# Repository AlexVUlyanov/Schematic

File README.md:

# Schematic
Schematic module
- папка SMART LOCK UK - проект модуля доступа с базой данных по RFID - картам. Схемотехника выполнена в EAGLE CAD. В качестве микроконтроллера используется stm8L. Прогрманное обеспечение на МК выпонено в среде IAR язык С. Программно аппаратный комплекс делает учет времени входа и выхода сотрудника с занисением в баззу даных в виде файла. Программное обеспечения для ПК верхний уровень выполена в среде LABVIEW.
- Analog PID control - схемная реализация аналоговго ПИД регулятра на операционных усилителях EAGLE CAD.
- MIFA 868 MHz - антенна на чатоту 868 МГц модель в Ansys HFSS. 
- MIFA 2400 MHz - антенна на чатоту 2400 МГц модель в Ansys HFSS + согласование LC.
- AWR_Design_filter - пример заграждающего фильтра на 5 ГГц микрополосковый, среда разработки Cadence AWR Design Environment.
- GPS_patch_ceramic - пример модели GPS антенны и ее характеристики (Ansys) 
- Concentrator устройство обеспечивает чтение выходов типа сухой контакт сигнализаций и позволяет считывать их используя интерфейс Modbus RTU (RS-485). (Altium)
- Проект Horseradish PI - одноплатный компьбтер на базе SoC Allwinner H3, выполненный в OrCad Cadence.
- Altium_RK3588 - импортированный проект DEMO board RK3588 + топология печатного узла.

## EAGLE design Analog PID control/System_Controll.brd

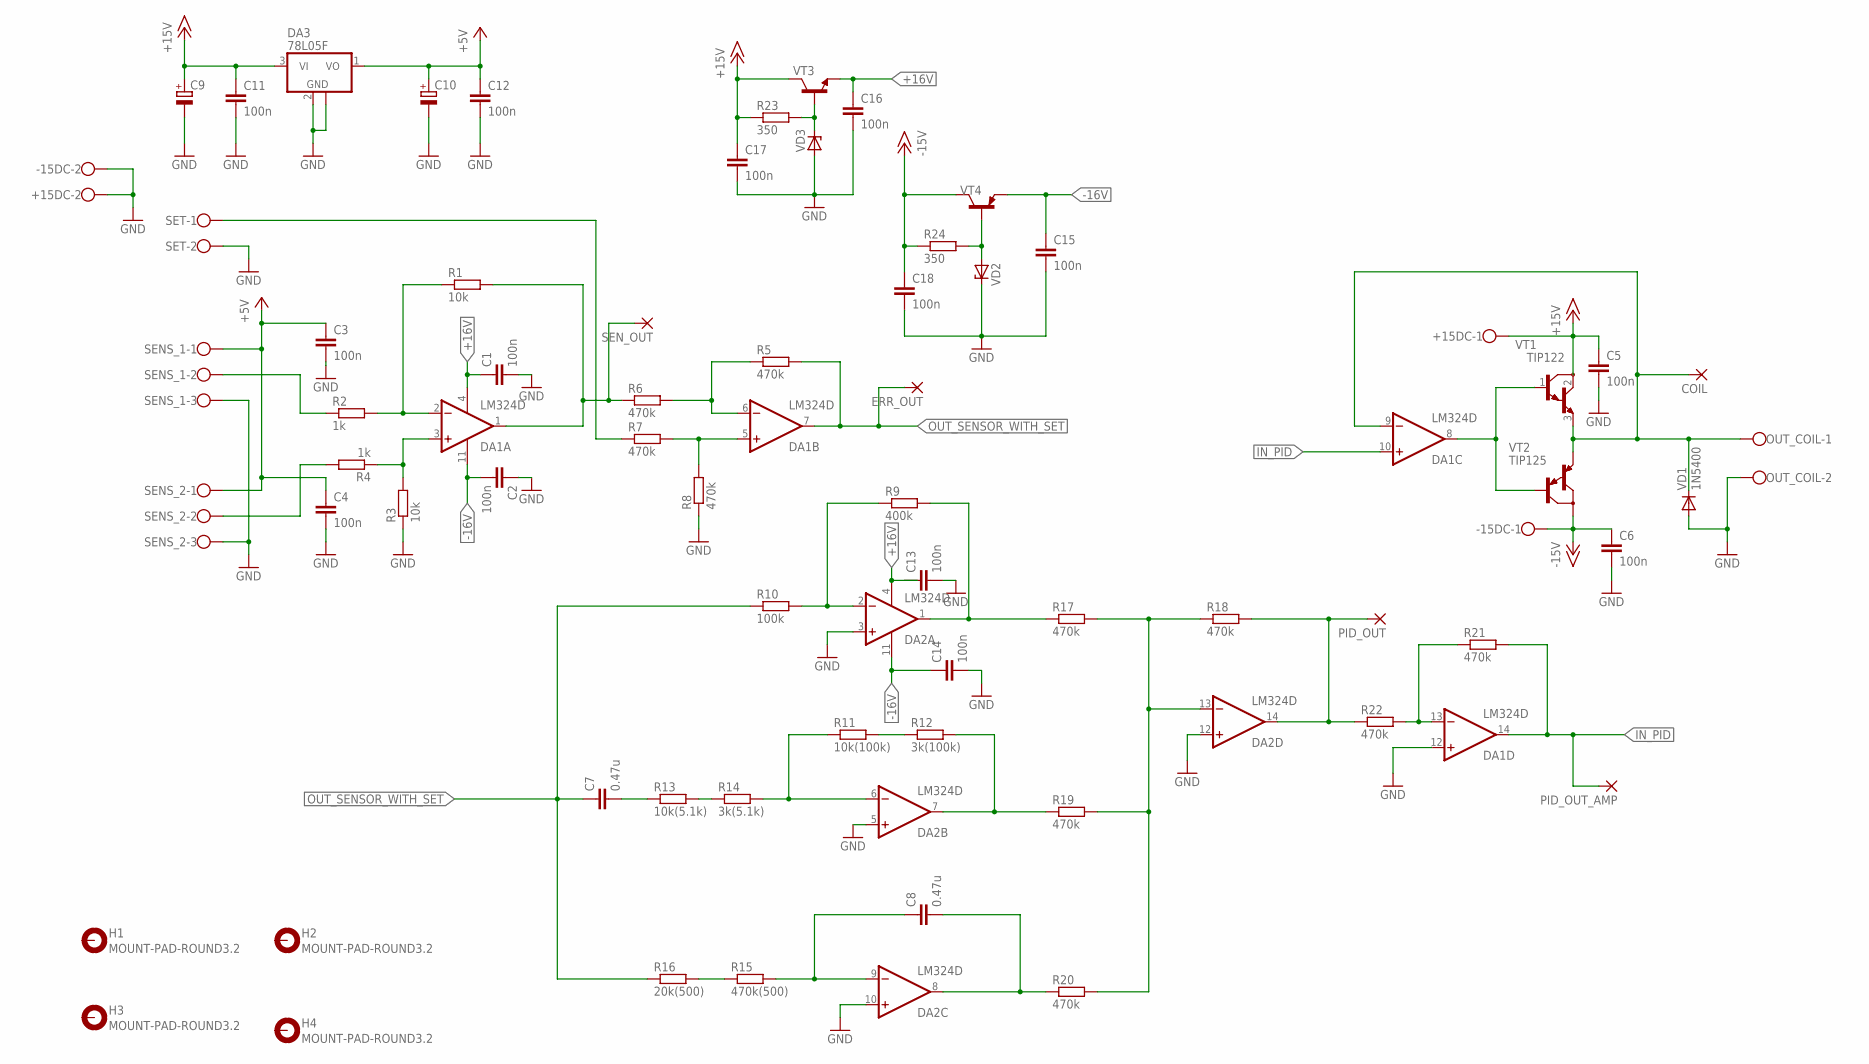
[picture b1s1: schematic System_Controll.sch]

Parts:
+15DC: W237-102
-15DC: W237-102
C1, C2, C3, C4, C5, C6, C11, C12, C13, C14, C15, C16, C17, C18: 100n; C1206
C7, C8: 0.47u; C1206
C9, C10: CPOL-EUE2,5-6; E2,5-6
COIL: PW_PAD
DA1, DA2: LM324D; SO14
DA3: 78L05F; SOT89
ERR_OUT: PW_PAD
H1, H2, H3, H4: MOUNT-PAD-ROUND3.2; 3,2-PAD
OUT_COIL: DG350-3.5-02P
PID_OUT: PW_PAD
PID_OUT_AMP: PW_PAD
R1, R3: 10k; M1206
R2, R4: 1k; M1206
R5, R6, R7, R8, R17, R18, R19, R20, R21, R22: 470k; M1206
R9: 400k; M1206
R10: 100k; M1206
R11: 10k(100k); M1206
R12: 3k(100k); M1206
R13: 10k(5.1k); M1206
R14: 3k(5.1k); M1206
R15: 470k(500); M1206
R16: 20k(500); M1206
R23, R24: 350; M1206
SENS_1, SENS_2: DG350-3.5-03P
SEN_OUT: PW_PAD
SET: DG350-3.5-02P
VD1: 1N5400; DO201-15
VD2, VD3: ZENER-DIODEDO41Z10; DO41Z10
VT1: TIP122; TO220
VT2: TIP125; TO220
VT3: BC847ALT1SMD; SOT23
VT4: BC807-16LT1SMD; SOT23-BEC

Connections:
+5V: C3.1, C4.1, C10.+, C12.1, DA3.1 (VO), SENS_1.1, SENS_2.1
+15V: +15DC.1, C5.1, C9.+, C11.1, C17.1, DA3.3 (VI), R23.1, VT1.2 (C), VT3.3 (C)
+16V: C1.1, C13.1, C16.1, DA1.4 (V+), DA2.4 (V+), VT3.2 (E)
-15V: -15DC.1, C6.1, C18.1, R24.1, VT2.2 (C), VT4.C
-16V: C2.2, C14.1, C15.1, DA1.11 (V-), DA2.11 (V-), VT4.E
COIL_OUT: COIL.P$1, DA1.9 (-IN), OUT_COIL.1, VD1.C, VT1.3 (E), VT2.3 (E)
GND: +15DC.2, -15DC.2, C1.2, C2.1, C3.2, C4.2, C5.2, C6.2, C9.-, C10.-, C11.2, C12.2, C13.2, C14.2, C15.2, C16.2, C17.2, C18.2, DA1.12 (+IN), DA2.3 (+IN), DA2.5 (+IN), DA2.10 (+IN), DA2.12 (+IN), DA3.2 (GND), DA3.2@1 (GND), OUT_COIL.2, R3.1, R8.1, SENS_1.3, SENS_2.3, SET.2, VD1.A, VD2.C, VD3.A
IN_PID: DA1.10 (+IN), DA1.14 (OUT), PID_OUT_AMP.P$1, R21.2
unnamed: DA1.1 (OUT), R1.2, R6.1, SEN_OUT.P$1
unnamed: DA1.2 (-IN), R1.1, R2.2
unnamed: DA1.3 (+IN), R3.2, R4.1
unnamed: R2.1, SENS_1.2
unnamed: R4.2, SENS_2.2
unnamed: DA2.2 (-IN), R9.1, R10.2
unnamed: R7.1, SET.1
unnamed: DA1.6 (-IN), R5.1, R6.2
unnamed: DA1.5 (+IN), R7.2, R8.2
unnamed: DA1.8 (OUT), VT1.1 (B), VT2.1 (B)
unnamed: DA2.1 (OUT), R9.2, R17.1
unnamed: R11.2, R12.1
unnamed: DA2.7 (OUT), R12.2, R19.1
unnamed: DA2.6 (-IN), R11.1, R14.2
unnamed: R13.2, R14.1
unnamed: C7.2, R13.1
unnamed: R24.2, VD2.A, VT4.B
unnamed: C8.2, DA2.8 (OUT), R20.1
unnamed: C8.1, DA2.9 (-IN), R15.2
unnamed: R15.1, R16.2
unnamed: DA2.13 (-IN), R17.2, R18.1, R19.2, R20.2
unnamed: DA2.14 (OUT), PID_OUT.P$1, R18.2, R22.1
unnamed: DA1.13 (-IN), R21.1, R22.2
unnamed: R23.2, VD3.C, VT3.1 (B)
OUT_SENSOR_WITH_SET: C7.1, DA1.7 (OUT), ERR_OUT.P$1, R5.2, R10.1, R16.1

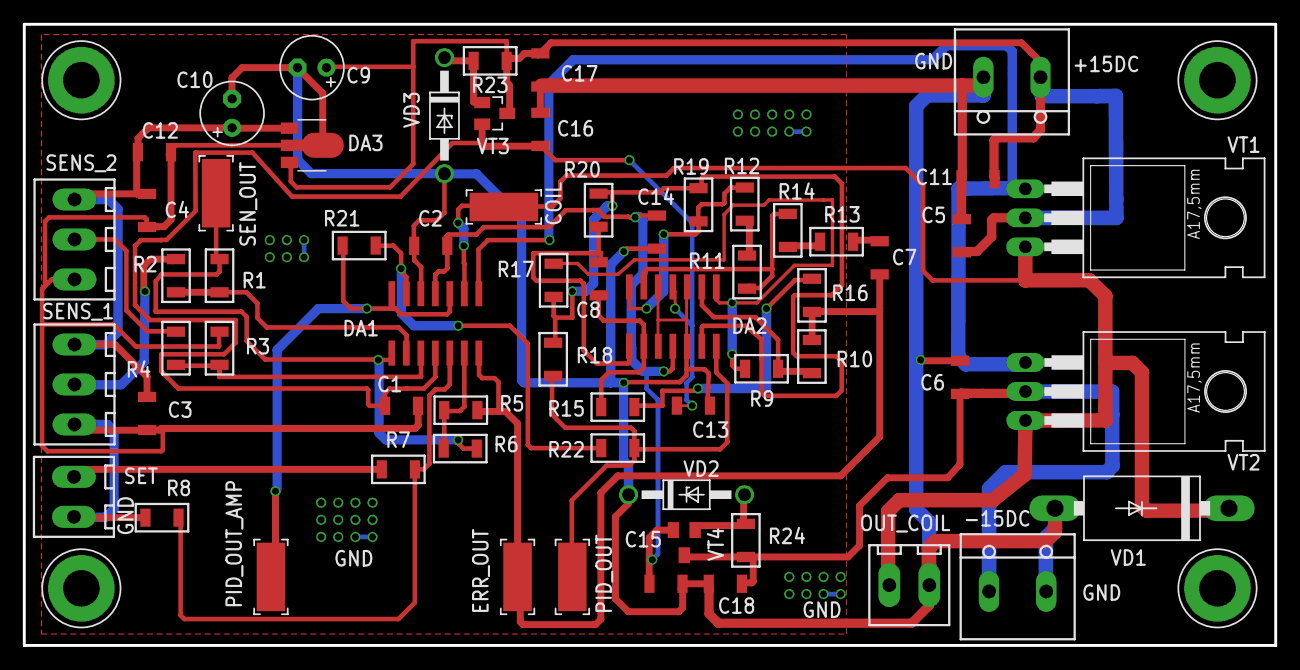
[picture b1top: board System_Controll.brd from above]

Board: 2 copper layers, 109.6 x 54.4 mm, 67 parts (0 on the bottom side), 33 nets.

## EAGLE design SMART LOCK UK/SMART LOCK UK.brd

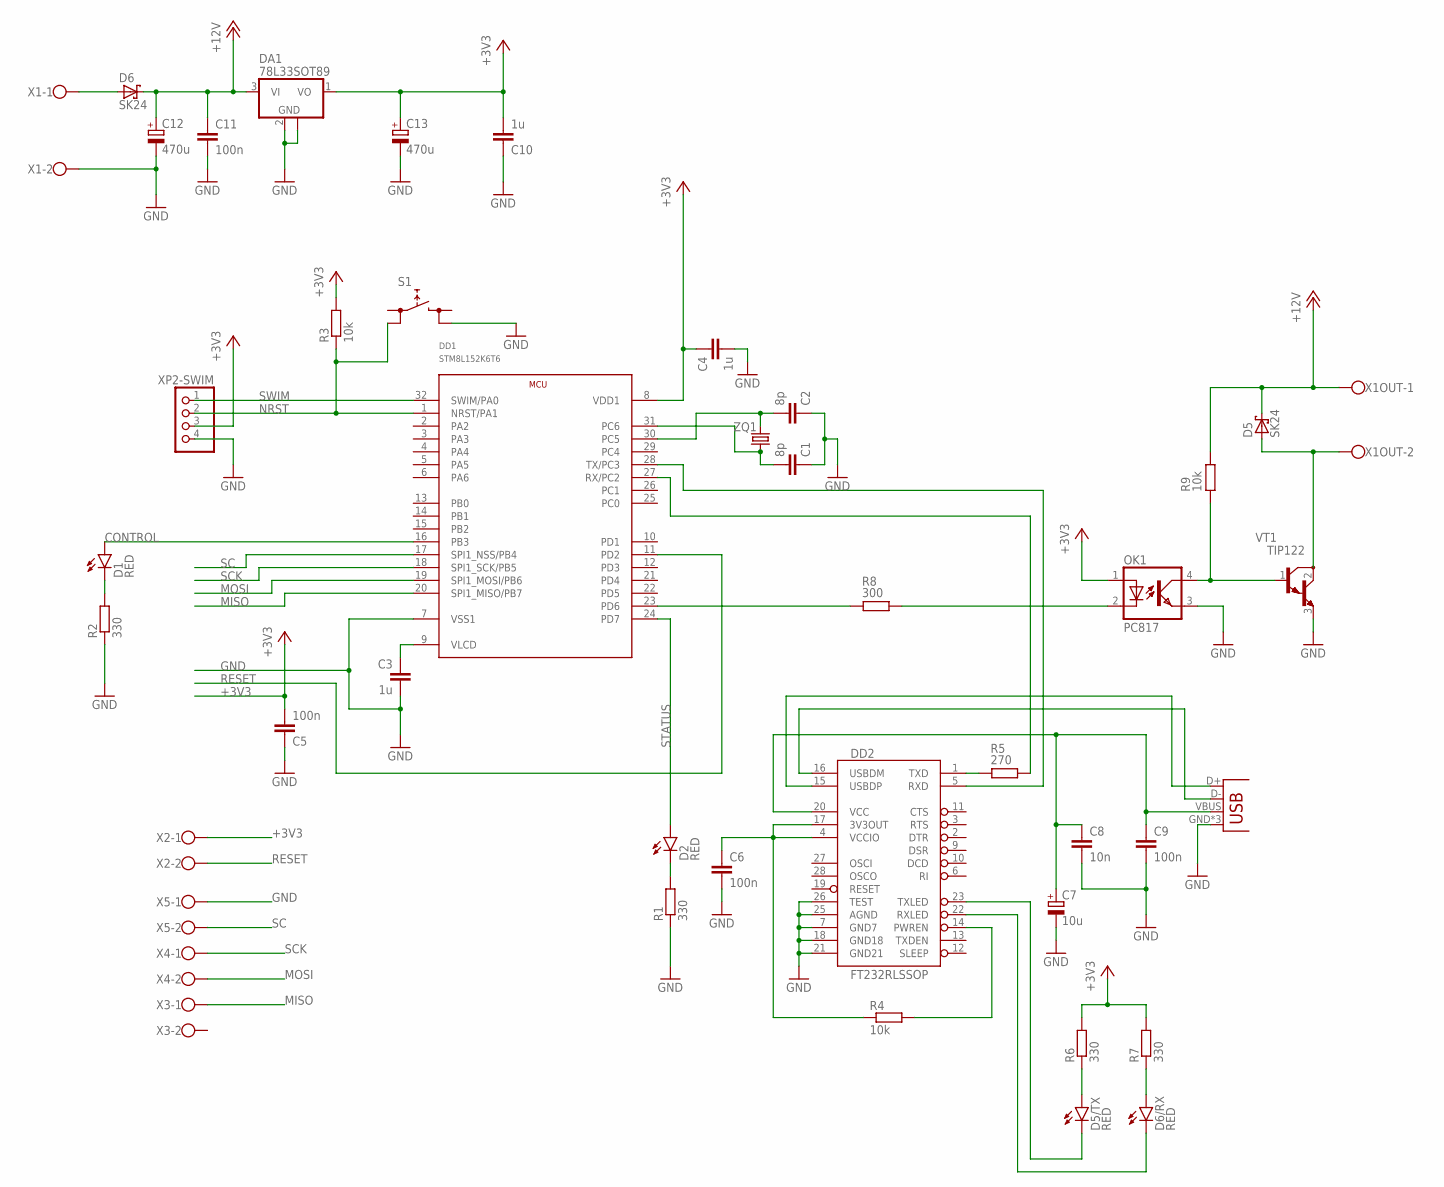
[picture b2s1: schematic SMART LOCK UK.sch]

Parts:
C1, C2: 8p; C1206
C3, C4, C10: 1u; C1206
C5, C6, C9, C11: 100n; C1206
C7: 10u; E2,5-5
C8: 10n; C1206
C12, C13: 470u; E3,5-8
D1, D2, D5/TX, D6/RX: RED; LED-1206
D5, D6: SK24; SMB
DA1: 78L33SOT89; SOT89
DD1: STM8L152K6T6; LQFP32-7X7
DD2: FT232RLSSOP; SSOP28DB
JP1: USB-B; USB-B-PTH
OK1: PC817; DIL04
R1, R2, R6, R7: 330; M1206
R3, R4, R9: 10k; M1206
R5: 270; M1206
R8: 300; M1206
S1: TACKT_SW_TH; TL1105
VT1: TIP122; TO220
X1, X1OUT: W237-102
X2, X3, X4, X5: DG350-3.5-02P
XP2-SWIM: PINHD-1X4; 1X04
ZQ1: CRYSTAL1MM20SS; MM20SS

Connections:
+3V3: C4.1, C5.2, C10.2, C13.+, DA1.1 (VO), DD1.8 (VDD1), OK1.1 (A), R3.2, R6.2, R7.2, X2.1, XP2-SWIM.3
+12V: C11.1, C12.+, D5.C, D6.C, DA1.3 (VI), R9.2, X1OUT.1
CONTROL: D1.A, DD1.16 (PB3)
GND: C1.1, C2.1, C3.2, C4.2, C5.1, C6.2, C7.-, C8.2, C9.2, C10.1, C11.2, C12.-, C13.-, DA1.2 (GND), DA1.2@1 (GND), DD1.7 (VSS1), DD2.7 (GND7), DD2.18 (GND18), DD2.21 (GND21), DD2.25 (AGND), DD2.26 (TEST), JP1.GND, JP1.S1 (GND), JP1.S2 (GND), OK1.3 (EMIT), R1.1, R2.1, S1.4 (1), VT1.3 (E), X1.2, X5.1, XP2-SWIM.4
MISO: DD1.20 (SPI1_MISO/PB7), X3.1
MOSI: DD1.19 (SPI1_MOSI/PB6), X4.2
unnamed: DD1.28 (TX/PC3), DD2.5 (RXD)
unnamed: C1.2, DD1.31 (PC6), ZQ1.1
unnamed: C3.1, DD1.9 (VLCD)
unnamed: D5/TX.A, R6.1
unnamed: D6/RX.A, R7.1
unnamed: D5/TX.C, DD2.23 (TXLED)
unnamed: D6/RX.C, DD2.22 (RXLED)
unnamed: D5.A, VT1.2 (C), X1OUT.2
unnamed: D2.C, R1.2
unnamed: D1.C, R2.2
unnamed: OK1.4 (COL), R9.1, VT1.1 (B)
unnamed: OK1.2 (C), R8.2
unnamed: DD1.23 (PD6), R8.1
unnamed: D6.A, X1.1
unnamed: C7.+, C8.1, C9.1, DD2.20 (VCC), JP1.VBUS
unnamed: DD1.27 (RX/PC2), R5.2
unnamed: C2.2, DD1.30 (PC5), ZQ1.4 (2)
unnamed: DD2.16 (USBDM), JP1.D-
unnamed: DD2.15 (USBDP), JP1.D+
unnamed: C6.1, DD2.4 (VCCIO), DD2.17 (3V3OUT), R4.1
unnamed: DD2.14 (PWREN), R4.2
unnamed: DD2.1 (TXD), R5.1
NRST: DD1.1 (NRST/PA1), R3.1, S1.3 (0), XP2-SWIM.2
RESET: DD1.11 (PD2), X2.2
SC: DD1.17 (SPI1_NSS/PB4), X5.2
SCK: DD1.18 (SPI1_SCK/PB5), X4.1
STATUS: D2.A, DD1.24 (PD7)
SWIM: DD1.32 (SWIM/PA0), XP2-SWIM.1

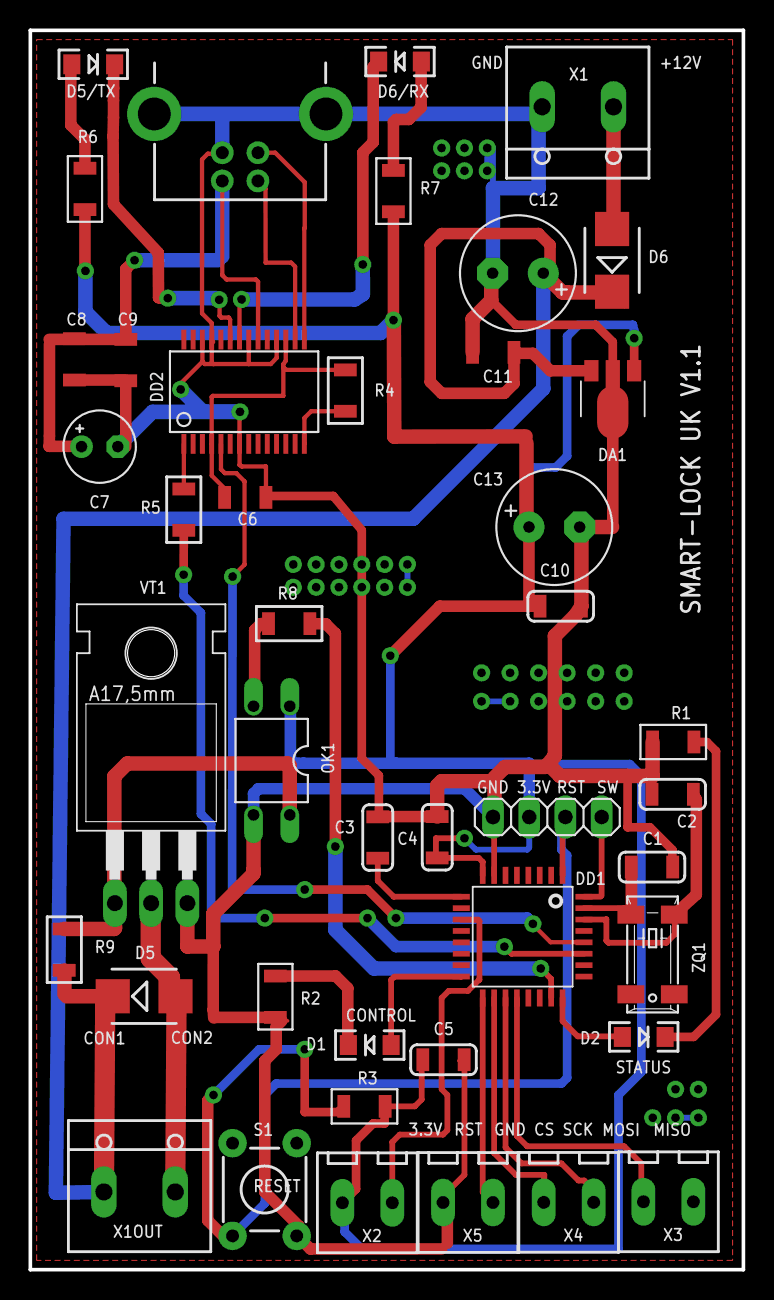
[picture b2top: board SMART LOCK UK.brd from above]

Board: 2 copper layers, 50.0 x 86.9 mm, 43 parts (0 on the bottom side), 34 nets.

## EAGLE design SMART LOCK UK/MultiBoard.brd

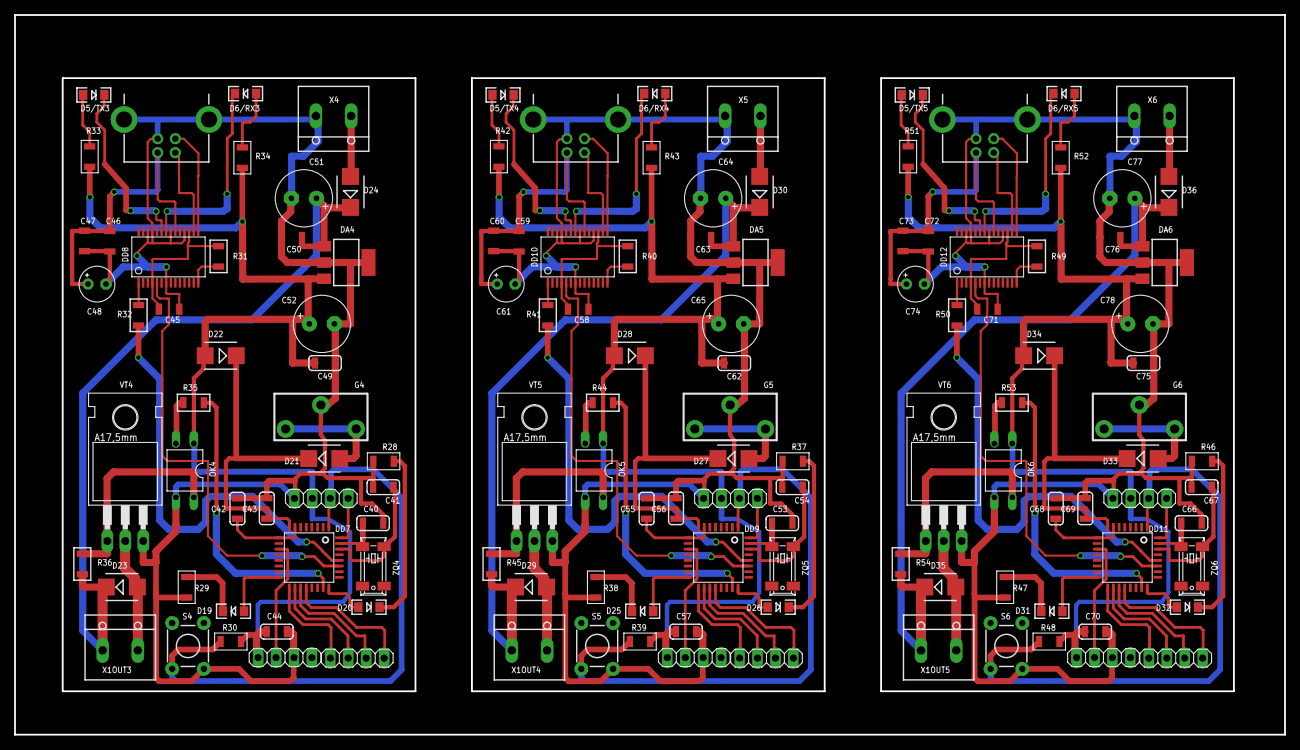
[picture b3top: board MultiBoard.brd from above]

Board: 2 copper layers, 180.0 x 102.0 mm, 132 parts (0 on the bottom side), 108 nets.

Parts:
C40, C41, C53, C54, C66, C67: 8p; C1206
C42, C43, C49, C55, C56, C62, C68, C69, C75: 1u; C1206
C44, C45, C46, C50, C57, C58, C59, C63, C70, C71, C72, C76: 100n; C1206
C47, C60, C73: 10n; C1206
C48, C61, C74: 10u; E2,5-5
C51, C52, C64, C65, C77, C78: 470u; E3,5-8
D5/TX3, D5/TX4, D5/TX5, D6/RX3, D6/RX4, D6/RX5, D19, D20, D25, D26, D31, D32: RED; LED-1206
D21, D22, D23, D24, D27, D28, D29, D30, D33, D34, D35, D36: SK24; SMB
DA4, DA5, DA6: APU1206H-33; SOT223
DD7, DD9, DD11: STM8L152K6T6; LQFP32-7X7
DD8, DD10, DD12: FT232RLSSOP; SSOP28DB
G4, G5, G6: BAT_3VCH-74; CH74
JP4, JP5, JP6: USB-B; USB-B-PTH
OK4, OK5, OK6: PC817; DIL04
R28, R29, R33, R34, R37, R38, R42, R43, R46, R47, R51, R52: 330; M1206
R30, R31, R39, R40, R48, R49: 10k; M1206
R32, R41, R50: 270; M1206
R35, R36, R44, R45, R53, R54: 1k; M1206
S4, S5, S6: TL1105
VT4, VT5, VT6: TIP122; TO220
X1OUT3, X1OUT4, X1OUT5, X4, X5, X6: W237-102
XP1.1-SPI3, XP1.1-SPI4, XP1.1-SPI5, XP1.2-SPI3, XP1.2-SPI4, XP1.2-SPI5, XP2-SWIM3, XP2-SWIM4, XP2-SWIM5: 1X04
ZQ4, ZQ5, ZQ6: MM20SS

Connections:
+3V4: C44.2, C49.2, C52.+, D22.A, DA4.3, OK4.1, R30.2, R33.2, R34.2, XP1.2-SPI3.4, XP2-SWIM3.3
+3V5: C57.2, C62.2, C65.+, D28.A, DA5.3, OK5.1, R39.2, R42.2, R43.2, XP1.2-SPI4.4, XP2-SWIM4.3
+3V6: C70.2, C75.2, C78.+, D34.A, DA6.3, OK6.1, R48.2, R51.2, R52.2, XP1.2-SPI5.4, XP2-SWIM5.3
+12V3: C50.1, C51.+, D23.C, D24.C, DA4.1, R36.2, X1OUT3.1
+12V4: C63.1, C64.+, D29.C, D30.C, DA5.1, R45.2, X1OUT4.1
+12V5: C76.1, C77.+, D35.C, D36.C, DA6.1, R54.2, X1OUT5.1
CONTROL3: D19.A, DD7.16
CONTROL4: D25.A, DD9.16
CONTROL5: D31.A, DD11.16
FT_RXD3: DD7.28, R32.2
FT_RXD4: DD9.28, R41.2
FT_RXD5: DD11.28, R50.2
FT_TXD3: DD7.27, DD8.5
FT_TXD4: DD9.27, DD10.5
FT_TXD5: DD11.27, DD12.5
GND3: C40.1, C41.1, C42.2, C43.2, C44.1, C45.2, C46.2, C47.2, C48.-, C49.1, C50.2, C51.-, C52.-, DA4.2, DA4.4, DD8.7, DD8.18, DD8.21, DD8.25, DD8.26, G4.P$3-, JP4.GND, JP4.S1, JP4.S2, OK4.3, R28.1, R29.1, S4.4, VT4.3, X4.2, XP1.2-SPI3.2, XP2-SWIM3.4
GND4: C53.1, C54.1, C55.2, C56.2, C57.1, C58.2, C59.2, C60.2, C61.-, C62.1, C63.2, C64.-, C65.-, DA5.2, DA5.4, DD10.7, DD10.18, DD10.21, DD10.25, DD10.26, G5.P$3-, JP5.GND, JP5.S1, JP5.S2, OK5.3, R37.1, R38.1, S5.4, VT5.3, X5.2, XP1.2-SPI4.2, XP2-SWIM4.4
GND5: C66.1, C67.1, C68.2, C69.2, C70.1, C71.2, C72.2, C73.2, C74.-, C75.1, C76.2, C77.-, C78.-, DA6.2, DA6.4, DD12.7, DD12.18, DD12.21, DD12.25, DD12.26, G6.P$3-, JP6.GND, JP6.S1, JP6.S2, OK6.3, R46.1, R47.1, S6.4, VT6.3, X6.2, XP1.2-SPI5.2, XP2-SWIM5.4
MISO3: DD7.20, XP1.1-SPI3.4
MISO4: DD9.20, XP1.1-SPI4.4
MISO5: DD11.20, XP1.1-SPI5.4
MOSI3: DD7.19, XP1.1-SPI3.3
MOSI4: DD9.19, XP1.1-SPI4.3
MOSI5: DD11.19, XP1.1-SPI5.3
unnamed: C40.2, DD7.31, ZQ4.1
unnamed: C42.1, DD7.7, DD7.9
unnamed: D20.C, R28.2
unnamed: D19.C, R29.2
unnamed: D21.A, G4.P$1+, G4.P$2+
unnamed: C43.1, D21.C, D22.C, DD7.8
unnamed: C46.1, C47.1, C48.+, DD8.20, JP4.VBUS
unnamed: DD8.16, JP4.D-
unnamed: DD8.15, JP4.D+
unnamed: C45.1, DD8.4, DD8.17, R31.1
unnamed: DD8.14, R31.2
unnamed: DD8.1, R32.1
unnamed: D5/TX3.A, R33.1
unnamed: D6/RX3.A, R34.1
unnamed: D5/TX3.C, DD8.23
unnamed: D6/RX3.C, DD8.22
unnamed: D23.A, VT4.2, X1OUT3.2
unnamed: OK4.2, R35.2
unnamed: DD7.23, R35.1
unnamed: OK4.4, R36.1, VT4.1
unnamed: D24.A, X4.1
unnamed: C41.2, DD7.30, ZQ4.4
unnamed: C53.2, DD9.31, ZQ5.1
unnamed: C55.1, DD9.7, DD9.9
unnamed: D26.C, R37.2
unnamed: D25.C, R38.2
unnamed: D27.A, G5.P$1+, G5.P$2+
unnamed: C56.1, D27.C, D28.C, DD9.8
unnamed: C59.1, C60.1, C61.+, DD10.20, JP5.VBUS
unnamed: DD10.16, JP5.D-
unnamed: DD10.15, JP5.D+
unnamed: C58.1, DD10.4, DD10.17, R40.1
unnamed: DD10.14, R40.2
unnamed: DD10.1, R41.1
unnamed: D5/TX4.A, R42.1
unnamed: D6/RX4.A, R43.1
unnamed: D5/TX4.C, DD10.23
unnamed: D6/RX4.C, DD10.22
unnamed: D29.A, VT5.2, X1OUT4.2
unnamed: OK5.2, R44.2
unnamed: DD9.23, R44.1
unnamed: OK5.4, R45.1, VT5.1
unnamed: D30.A, X5.1
unnamed: C54.2, DD9.30, ZQ5.4
unnamed: C66.2, DD11.31, ZQ6.1
unnamed: C68.1, DD11.7, DD11.9
unnamed: D32.C, R46.2
unnamed: D31.C, R47.2
unnamed: D33.A, G6.P$1+, G6.P$2+
unnamed: C69.1, D33.C, D34.C, DD11.8
unnamed: C72.1, C73.1, C74.+, DD12.20, JP6.VBUS
unnamed: DD12.16, JP6.D-
unnamed: DD12.15, JP6.D+
unnamed: C71.1, DD12.4, DD12.17, R49.1
unnamed: DD12.14, R49.2
unnamed: DD12.1, R50.1
unnamed: D5/TX5.A, R51.1
unnamed: D6/RX5.A, R52.1
unnamed: D5/TX5.C, DD12.23
unnamed: D6/RX5.C, DD12.22
unnamed: D35.A, VT6.2, X1OUT5.2
unnamed: OK6.2, R53.2
unnamed: DD11.23, R53.1
unnamed: OK6.4, R54.1, VT6.1
unnamed: D36.A, X6.1
unnamed: C67.2, DD11.30, ZQ6.4
NRST3: DD7.1, R30.1, S4.3, XP2-SWIM3.2
NRST4: DD9.1, R39.1, S5.3, XP2-SWIM4.2
NRST5: DD11.1, R48.1, S6.3, XP2-SWIM5.2
RESET3: DD7.11, XP1.2-SPI3.3
RESET4: DD9.11, XP1.2-SPI4.3
RESET5: DD11.11, XP1.2-SPI5.3
SC3: DD7.17, XP1.1-SPI3.1
SC4: DD9.17, XP1.1-SPI4.1
SC5: DD11.17, XP1.1-SPI5.1
SCK3: DD7.18, XP1.1-SPI3.2
SCK4: DD9.18, XP1.1-SPI4.2
SCK5: DD11.18, XP1.1-SPI5.2
STATUS3: D20.A, DD7.24
STATUS4: D26.A, DD9.24
STATUS5: D32.A, DD11.24
SWIM3: DD7.32, XP2-SWIM3.1
SWIM4: DD9.32, XP2-SWIM4.1
SWIM5: DD11.32, XP2-SWIM5.1

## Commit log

2022-07-19 add schematic and programms MCU (IAR-C) and PC (Labview)
2022-11-26 add analog PID control
2023-03-13 add calc and model MIFA 868MHz Ansys HFSS
2023-03-19 add calc and model MIFA 2400MHz Ansys HFSS
2023-04-09 add filter AWE Design
2023-04-09 add filter 5GHz AWE Design
2023-04-16 add GPS patch ceramic
2023-05-01 add project concentrator
2023-05-13 Add 01_maine_block - Allwiner H3 systems
2023-05-14 add Power - IN +5V to +5V_VCC
2023-05-20 add DRAM VCC PWR
2023-05-20 add lib components
2023-05-21 add lib PWR CPUX
2023-05-27 Schematic PWR and PWR Tree
2023-06-04 lib Allwinner H3 - GPIO port A
2023-06-04 lib Allwinner H3 - GPIO section add
2023-06-10 lib Allwinner H3 - HDMI, SYS, POWER, ETHERNET, USB - section add
2023-06-17 Shchematic cpu part 1 - HDMI, MIC, ETHERNET, LIN/OUT, TF
2023-06-24 Shchematic add mSD, Wi-Fi
2023-06-25 Shchematic add MIC, LINOUT R/L
2023-07-02 Shchematic add Ethernet ISO
2023-07-05 Shchematic add HDMI
2024-01-04 ADD DDR3 H5TQ4G63AFR-PBC Library simbol
2024-01-05 DDR3 VCC-DRAM VCC-SVREF SCK
2024-01-06 DDR3 8Gb connect to SoC, Wi-fi module connetc to SoC
2024-01-08 H3 POWER connection
2024-01-08 H3 POWER add capacitors
2024-01-08 Add UART1 - connector, PWR-LED, IR-RX connector
2024-01-13 Add USB-SYS
2024-01-14 Select NAND FLASH HY27UG088G5M-TPCB
2024-01-20 Schematic NAND FLASH HY27UG088G5M-TPCB
2025-03-15 imported demo board RK3588
2025-03-15 Alegro cadence to Altiume pcb
